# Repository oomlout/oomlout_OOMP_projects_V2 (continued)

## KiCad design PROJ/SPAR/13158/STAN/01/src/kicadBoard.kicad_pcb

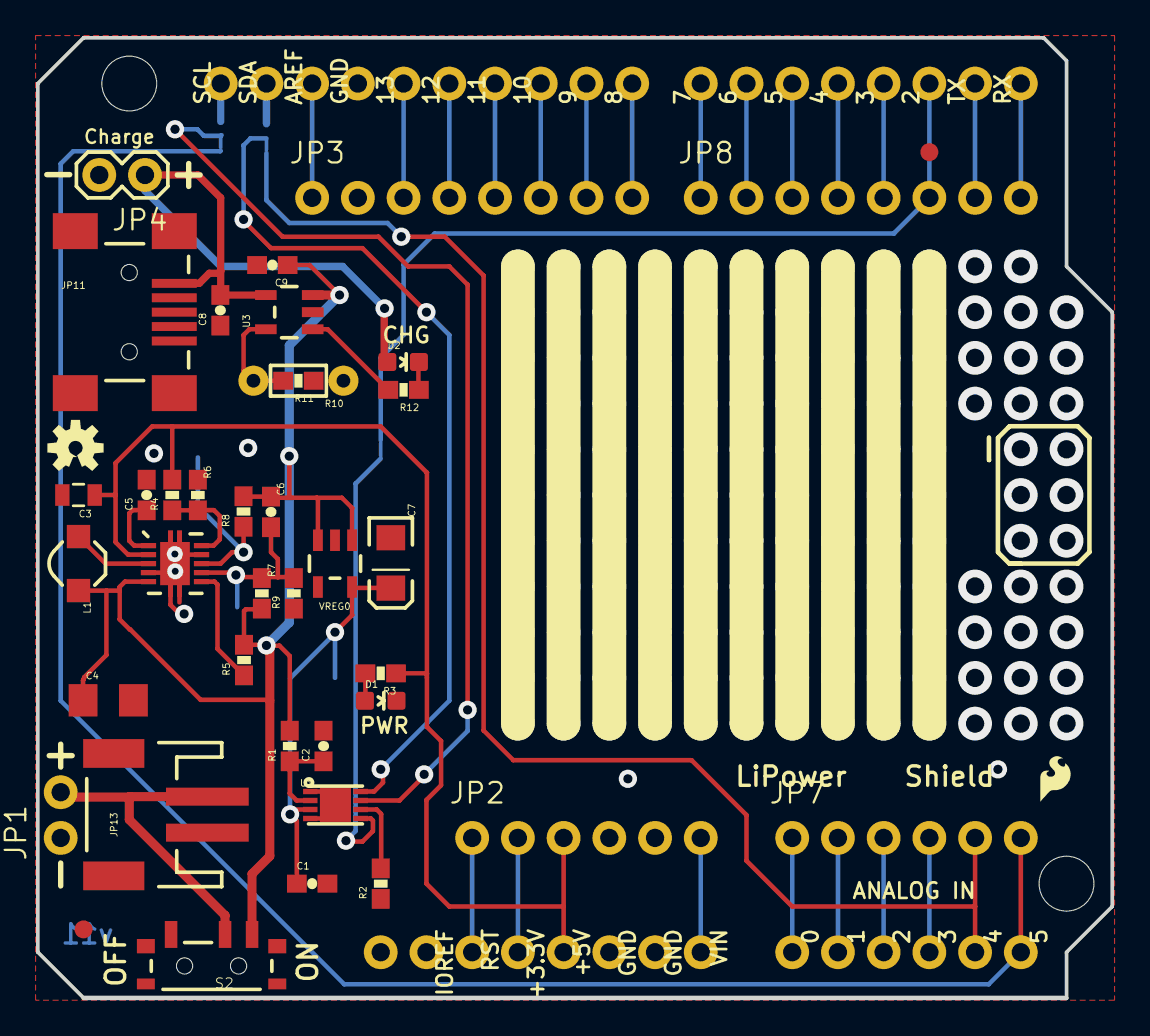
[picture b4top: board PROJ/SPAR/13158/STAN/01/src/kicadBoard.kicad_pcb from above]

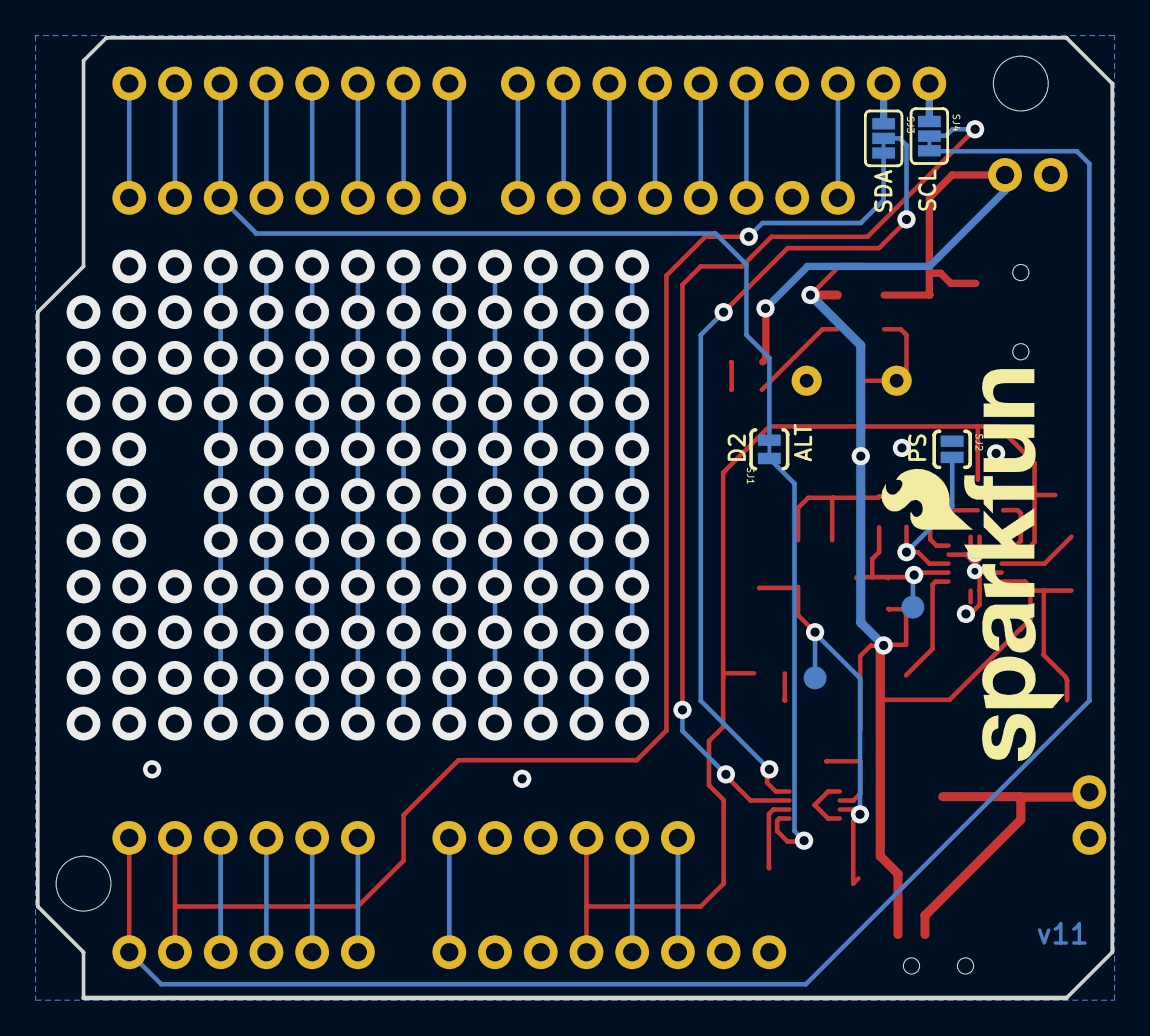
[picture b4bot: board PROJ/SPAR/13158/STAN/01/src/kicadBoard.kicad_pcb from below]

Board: 2 copper layers, 59.7 x 53.3 mm, 52 parts (7 on the bottom side), 47 nets.

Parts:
C1: 10nF; 0603-CAP
C2: 1uF; 0603-CAP
C3: 22uF; 0805
C4: 10uF; 1206
C5, C6: 0.1uF; 0603-CAP
C7: 10uF; EIA3216
C8, C9: 4.7uF; 0603-CAP
D1, D2: RED; LED-0603
FID1, FID2: FIDUCIAL1X2; FIDUCIAL-1X2
FRAME1: FRAME-LETTER; CREATIVE_COMMONS
JP1: 1X02_NO_SILK
JP2, JP7: 1X06_NO_SILK
JP3, JP8: 1X08_NO_SILK
JP4: M02PTH; 1X02
JP9, JP10: STAND-OFFTIGHT; STAND-OFF-TIGHT
JP11: USBSMD; USB-MINIB
JP13: JST-2-SMD
L1: 4.7uH, 1.2A; INDUCTOR_4.7UH
LOGO1: OSHW-LOGOS; OSHW-LOGO-S
LOGO2: SFE_LOGO_NAME_FLAME.2_INCH; SFE_LOGO_NAME_FLAME_.2
LOGO3: SFE_LOGO_FLAME.1_INCH; SFE_LOGO_FLAME_.1
R1: 1k; 0603-RES
R2: 4.7k; 0603-RES
R3, R12: 330; 0603-RES
R4: 2M; 0603-RES
R5, R8, R11: 10k; 0603-RES
R6: 220k; 0603-RES
R7: 2.0M; 0603-RES
R9: 200k; 0603-RES
R10: DNP; 1_6W-RES
S2: SWITCH-SPST-SMD-A
SJ1: SOLDERJUMPERTRACE; SJ_2S-TRACE
SJ2: PS; SJ_2S-NO
SJ3: SDA; PAD-JUMPER-3-2OF3_NC_BY_TRACE_YES_SILK_FULL_BOX
SJ4: SCL; PAD-JUMPER-3-2OF3_NC_BY_TRACE_YES_SILK_FULL_BOX
TP1, TP2: TEST-POINT3X5; PAD.03X.05
U1: MAX17043G+U; TDFN-8
U2: TPS61200; QFN-10_PAD
U3: MCP73831; SOT23-5
U4: ARDUINO_R3_SHIELD; UNO_R3_SHIELD
VREG0: MIC5205-3.3V; SOT23-5

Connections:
3.3-ARDUINO: JP2.2, U4.3.3V
3.3V: C1.1, C7.A, TP2.P$1, U1.3, VREG0.5
5V: C3.1, JP2.3, R3.1, R4.2, U2.2, U4.5V
A0: JP7.1, U4.A0
A1: JP7.2, U4.A1
A2: JP7.3, U4.A2
A3: JP7.4, U4.A3
ALT: SJ1.1, U1.5
AREF: JP3.1, U4.AREF
CELL: C2.1, R1.1, U1.2
D2: JP8.6, SJ1.2, U4.D2
D3: JP8.5, U4.D3
D4: JP8.4, U4.D4
D5: JP8.3, U4.D5
D6: JP8.2, U4.D6
D7: JP8.1, U4.D7
D8: JP3.8, U4.D8
D9: JP3.7, U4.D9
D10: JP3.6, U4.D10
D11: JP3.5, U4.D11
D12: JP3.4, U4.D12
D13: JP3.3, U4.D13
EN: R5.1, U2.6
FB: R4.1, R6.2, U2.10
GND: C1.2, C2.2, C3.2, C4.2, C5.2, C7.C, C8.1, C9.2, D1.C, JP1.1, JP2.4, JP2.5, JP3.2, JP4.2, JP11.GND, JP13.1, R2.1, R6.1, R9.1, R10.1, R11.1, SJ2.1, U1.1, U1.4, U1.EP, U2.4, U2.9, U2.11, U2.12, U2.13, U2.14, U2.15, U3.2, U4.GND@0, U4.GND@1, U4.GND@2, VREG0.2
unnamed: D1.A, R3.2
unnamed: L1.P$1, U2.3
unnamed: C5.1, U2.1
unnamed: D2.C, R12.1
unnamed: JP1.2, JP13.2, S2.2
unnamed: SJ3.2, U1.8
PROG: R10.2, R11.2, U3.5
PS: R8.1, SJ2.2, U2.8
QST: R2.2, U1.6
RST: JP2.1, U4.RES
RX: JP8.8, U4.RX
SCL: SJ4.2, U1.7
SCL-A5: JP7.6, SJ4.3, U4.A5
SCL-R3: SJ4.1, U4.SCL
SDA-A4: JP7.5, SJ3.3, U4.A4
SDA-R3: SJ3.1, U4.SDA
STAT: R12.2, U3.1
TX: JP8.7, U4.TX
UVLO: C6.2, R7.1, R9.2, TP1.P$1, U2.7
VBATT: C4.1, C6.1, C9.1, L1.P$2, R1.2, R5.2, R7.2, R8.2, S2.1, U2.5, U3.3, VREG0.1, VREG0.3
VBUS: C8.2, D2.A, JP4.1, JP11.VBUS, U3.4
VIN: JP2.6, U4.VIN

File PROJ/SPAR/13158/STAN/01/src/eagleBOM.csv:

"Part";"Value";"Device";"Package";"Description";"PROD-ID";"PROD_ID";"VALUE";
"C1";"10nF";"10NF/10000PF-50V-10%(0603)";"0603-CAP";"CAP-00867";"";"CAP-00867";"10nF";
"C2";"1uF";"1.0UF-16V-10%(0603)";"0603-CAP";"CAP-00868";"";"CAP-00868";"1.0uF";
"C3";"22uF";"22UF-6.3V-20%(0805)";"0805";"CAP-08402";"";"CAP-08402";"22uF";
"C4";"10uF";"10UF-6.3V-20%(1206)";"1206";"CAP-10057";"";"CAP-10057";"10uF";
"C5";"0.1uF";"0.1UF-25V(+80/-20%)(0603)";"0603-CAP";"CAP-00810";"";"CAP-00810";"0.1uF";
"C6";"0.1uF";"0.1UF-25V(+80/-20%)(0603)";"0603-CAP";"CAP-00810";"";"CAP-00810";"0.1uF";
"C7";"10uF";"10UF-16V-10%(TANT)";"EIA3216";"CAP-00811";"";"CAP-00811";"10uF";
"C8";"4.7uF";"4.7UF-6.3V-10%(0603)0603";"0603-CAP";"CAP-08280";"";"CAP-08280";"4.7uF";
"C9";"4.7uF";"4.7UF-6.3V-10%(0603)0603";"0603-CAP";"CAP-08280";"";"CAP-08280";"4.7uF";
"D1";"RED";"LED-RED0603";"LED-0603";"Assorted Red LEDs";"";"DIO-00819";"RED";
"D2";"RED";"LED-RED0603";"LED-0603";"Assorted Red LEDs";"";"DIO-00819";"RED";
"FID1";"FIDUCIAL1X2";"FIDUCIAL1X2";"FIDUCIAL-1X2";"Fiducial Alignment Points";"";"";"";
"FID2";"FIDUCIAL1X2";"FIDUCIAL1X2";"FIDUCIAL-1X2";"Fiducial Alignment Points";"";"";"";
"FRAME1";"FRAME-LETTER";"FRAME-LETTER";"CREATIVE_COMMONS";"Schematic Frame";"";"";"";
"JP1";"";"M021X02_NO_SILK";"1X02_NO_SILK";"Header 2";"";"";"";
"JP2";"";"M06NO_SILK";"1X06_NO_SILK";"Header 6";"";"";"";
"JP3";"";"M08NO_SILK";"1X08_NO_SILK";"Header 8";"";"";"";
"JP4";"M02PTH";"M02PTH";"1X02";"Standard 2-pin 0.1" header. Use with";"";"";"";
"JP7";"";"M06NO_SILK";"1X06_NO_SILK";"Header 6";"";"";"";
"JP8";"";"M08NO_SILK";"1X08_NO_SILK";"Header 8";"";"";"";
"JP9";"STAND-OFFTIGHT";"STAND-OFFTIGHT";"STAND-OFF-TIGHT";"Stand Off";"";"";"";
"JP10";"STAND-OFFTIGHT";"STAND-OFFTIGHT";"STAND-OFF-TIGHT";"Stand Off";"";"";"";
"JP11";"USBSMD";"USBSMD";"USB-MINIB";"USB Connectors";"";"CONN-08193";"";
"JP13";"";"JST_2MM_MALE";"JST-2-SMD";"Mates to single-cell LiPo batteries.";"";"CONN-08352";"";
"L1";"4.7uH, 1.2A";"INDUCTORINDUCTOR_4.7UH";"INDUCTOR_4.7UH";"Inductors";"";"NDUC-10146";"";
"LOGO1";"OSHW-LOGOS";"OSHW-LOGOS";"OSHW-LOGO-S";"Open Source Hardware Logo This logo indicates the piece of hardware it is found on incorporates a OSHW license and/or adheres to the definition of open source hardware found here: http://freedomdefined.org/OSHW";"";"";"";
"LOGO2";"SFE_LOGO_NAME_FLAME.2_INCH";"SFE_LOGO_NAME_FLAME.2_INCH";"SFE_LOGO_NAME_FLAME_.2";"SFE Logo, name and flame";"";"";"";
"LOGO3";"SFE_LOGO_FLAME.1_INCH";"SFE_LOGO_FLAME.1_INCH";"SFE_LOGO_FLAME_.1";"SFE Logo, flame only";"";"";"";
"R1";"1k";"1KOHM1/10W1%(0603)";"0603-RES";"RES-07856";"";"RES-07856";"1K";
"R2";"4.7k";"4.7KOHM1/10W1%(0603)";"0603-RES";"RES-07857";"";"RES-07857";"4.7K";
"R3";"330";"330OHM1/10W1%(0603)";"0603-RES";"RES-00818";"";"RES-00818";"330";
"R4";"2M";"2MOHMS-1/10W-1%(0603)";"0603-RES";"RES-10054";"";"RES-10054";"2.0M";
"R5";"10k";"10KOHM1/10W1%(0603)0603";"0603-RES";"RES-00824";"";"RES-00824";"10K";
"R6";"220k";"220KOHM1/10W1%(0603)";"0603-RES";"RES-08969";"";"RES-08969";"220k";
"R7";"2.0M";"2MOHMS-1/10W-1%(0603)";"0603-RES";"RES-10054";"";"RES-10054";"2.0M";
"R8";"10k";"10KOHM1/10W1%(0603)0603";"0603-RES";"RES-00824";"";"RES-00824";"10K";
"R9";"200k";"200KOHM1/10W1%(0603)200K";"0603-RES";"RES-09385";"";"RES-09385";"200k";
"R10";"DNP";"RESISTORPTH-1/6W";"1/6W-RES";"Resistor";"";"";"";
"R11";"10k";"10KOHM1/10W1%(0603)0603";"0603-RES";"RES-00824";"";"RES-00824";"10K";
"R12";"330";"330OHM1/10W1%(0603)";"0603-RES";"RES-00818";"";"RES-00818";"330";
"S2";"";"SWITCH-SPDT-SMD-A";"SWITCH-SPST-SMD-A";"SPDT Switch";"";"";"";
"SJ1";"SOLDERJUMPERTRACE";"SOLDERJUMPERTRACE";"SJ_2S-TRACE";"Solder Jumper";"";"";"";
"SJ2";"PS";"SOLDERJUMPERNO";"SJ_2S-NO";"Solder Jumper";"";"";"";
"SJ3";"SDA";"JUMPER-PAD-3-2OF3_NC_BY_TRACE";"PAD-JUMPER-3-2OF3_NC_BY_TRACE_YES_SILK_FULL_BOX";"";"";"";"";
"SJ4";"SCL";"JUMPER-PAD-3-2OF3_NC_BY_TRACE";"PAD-JUMPER-3-2OF3_NC_BY_TRACE_YES_SILK_FULL_BOX";"";"";"";"";
"TP1";"TEST-POINT3X5";"TEST-POINT3X5";"PAD.03X.05";"Bare copper test points for troubleshooting or ICT";"";"";"";
"TP2";"TEST-POINT3X5";"TEST-POINT3X5";"PAD.03X.05";"Bare copper test points for troubleshooting or ICT";"";"";"";
"U1";"MAX17043G+U";"MAX1704X";"TDFN-8";"MAX17043/MAX17044: Battery Fuel Guage (43 is 1cell, 44 is 2cell)";"IC-10399";"";"";
"U2";"TPS61200";"TPS61200";"QFN-10_PAD";"DC to DC Booster";"";"IC-10035";"";
"U3";"MCP73831";"MCP73831";"SOT23-5";"Miniature single cell, fully integrated Li-Ion, Li-polymer charge management controller";"";"IC-09995";"";
"U4";"ARDUINO_R3_SHIELD";"ARDUINO_R3_SHIELD";"UNO_R3_SHIELD";"Shield form compatible with the Arduino Uno R3.";"";"";"";
"VREG";"MIC5205-3.3V";"MIC52053.3V";"SOT23-5";"MIC5205 150mA vreg";"";"VREG-00822";"";

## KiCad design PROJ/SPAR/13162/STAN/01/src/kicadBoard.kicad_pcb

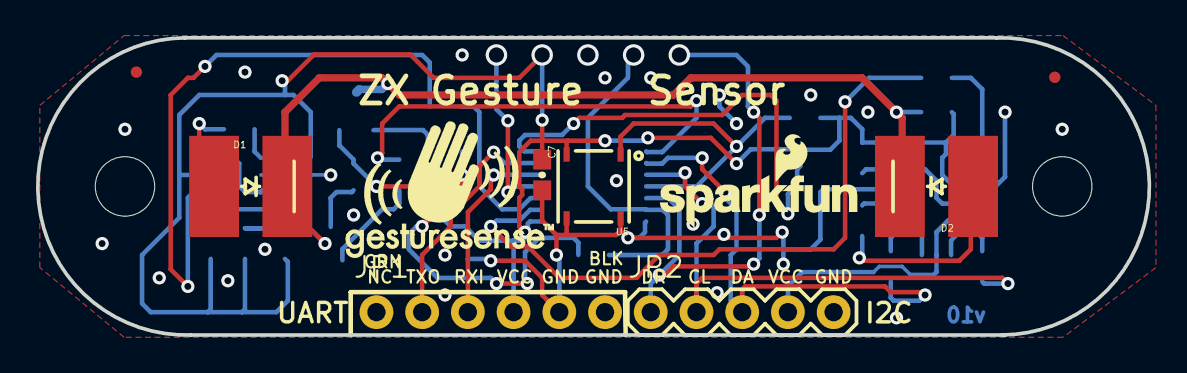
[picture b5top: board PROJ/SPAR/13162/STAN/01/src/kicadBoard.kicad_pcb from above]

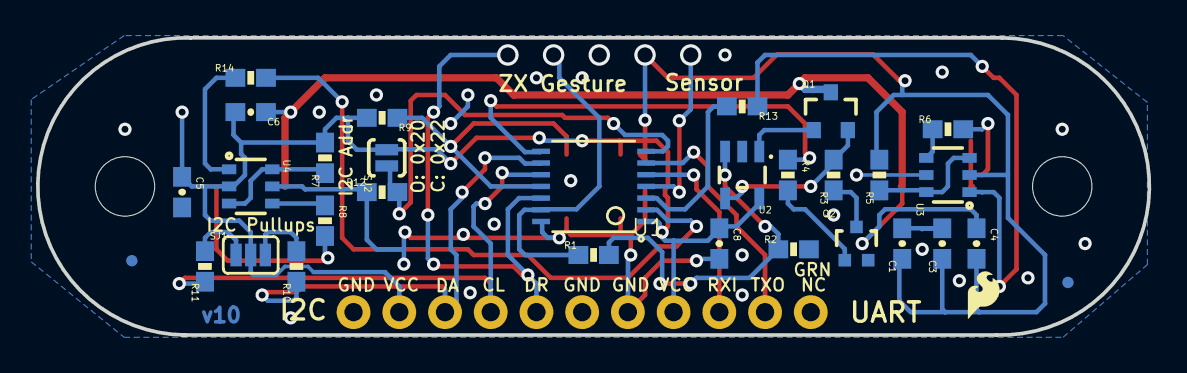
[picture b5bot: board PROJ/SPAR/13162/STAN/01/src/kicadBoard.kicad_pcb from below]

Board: 4 copper layers, 61.8 x 16.5 mm, 50 parts (36 on the bottom side), 30 nets.

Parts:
C1, C3, C5, C8: 0.1uF; 0603-CAP
C4, C6: 10nF; 0603-CAP
C7: 4.7uF; 0603-CAP
D1, D2: SFH4641SHORT2; SFH4641-SHORT2
FID1, FID2, FID3, FID4: FIDUCIALUFIDUCIAL; MICRO-FIDUCIAL
FRAME1: FRAME-LETTER; CREATIVE_COMMONS
JP1: 1X06_NO_SILK
JP2: 1X05
LOGO1: REVISION
LOGO2: SFE_LOGO_FLAME.1_INCH; SFE_LOGO_FLAME_.1
Q1: MMBT2222A; SOT23-3
Q2: MOSFET-NCHANNEL2N7002PW; SOT323
R1, R2, R5, R7: 100k; 0603-RES
R3: 1K 1%; 0603-RES
R4, R9, R13, R14: 1K; 0603-RES
R6, R8: 1; 0603-RES
R10, R11: 4.7K; 0603-RES
R12: 10K; 0603-RES
SJ1: JUMPER-PAD-3-NC_BY_PASTE; PAD-JUMPER-3-NC_BY_PASTE_YES_SILK_FULL_BOX
SJ2: JUMPER-PAD-2-NOYES_SILK; PAD-JUMPER-2-NO_YES_SILK
STANDOFF1, STANDOFF2: STAND-OFF
TP1, TP2, TP3, TP4, TP5: TEST-POINT3X4; PAD.03X.04
U1: PIC16F1823-14PINTSSOP; TSSOP14
U2: MCP6021T-E/OT; SOT23-5
U3, U4: DMC2700UDM; SOT26
U5: TSSP57038; TSOP572
U$5: SFE_LOGO_NAME_FLAME.1_INCH; SFE_LOGO_NAME_FLAME_.1
U$6: GESTURESENSE_LOGOSTEXT; GESTURESENSE_TEXT

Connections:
CARRIER: R4.1, U1.8
COMMON: C4.1, C6.1, D1.C, D2.C, Q1.3
EM1: R13.2, U1.3
EM2: R14.2, U1.2
GND: C1.2, C3.2, C5.2, C7.2, C8.2, JP1.5, JP1.6, JP2.5, Q2.2, R2.2, R12.1, TP3.P$1, U1.14, U2.2, U3.S1, U4.S1, U5.6, U5.8
I2C_ADDR: R12.2, SJ2.1, U1.7
I2C_SCL: JP2.2, R11.1, U1.10
I2C_SDA: JP2.3, R10.1, U1.9
ICSPCLK/DATA_RDY: JP2.1, TP5.P$1, U1.12
ICSPDAT/DACOUT: R1.1, TP4.P$1, U1.13
MCLR: TP1.P$1, U1.4
unnamed: R1.2, R2.1, U2.3
unnamed: Q1.2, R3.2, U2.4
unnamed: Q1.1, U2.1
unnamed: Q2.3, R3.1
unnamed: Q2.1, R4.2
unnamed: R6.1, U3.D2
unnamed: D1.A, R6.2
unnamed: R5.1, U3.D1, U3.G2
unnamed: R7.1, U4.D1, U4.G2
unnamed: R10.2, SJ1.3
unnamed: R8.1, U4.D2
unnamed: D2.A, R8.2
unnamed: R11.2, SJ1.1
unnamed: R13.1, U3.G1
unnamed: R14.1, U4.G1
RECEIVER: R9.1, U1.11, U5.1
UART_RX: JP1.2, U1.6
UART_TX: JP1.3, U1.5
VCC: C1.1, C3.1, C4.2, C5.1, C6.2, C7.1, C8.1, JP1.4, JP2.4, R5.2, R7.2, R9.2, SJ1.2, SJ2.2, TP2.P$1, U1.1, U2.5, U3.S2, U4.S2, U5.5

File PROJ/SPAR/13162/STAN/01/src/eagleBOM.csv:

"Part";"Value";"Device";"Package";"Description";"PROD_ID";"VALUE";
"C1";"0.1uF";"0.1UF-25V(+80/-20%)(0603)";"0603-CAP";"CAP-00810";"CAP-00810";"0.1uF";
"C3";"0.1uF";"0.1UF-25V(+80/-20%)(0603)";"0603-CAP";"CAP-00810";"CAP-00810";"0.1uF";
"C4";"10nF";"10NF/10000PF-50V-10%(0603)";"0603-CAP";"CAP-00867";"CAP-00867";"10nF";
"C5";"0.1uF";"0.1UF-25V(+80/-20%)(0603)";"0603-CAP";"CAP-00810";"CAP-00810";"0.1uF";
"C6";"10nF";"10NF/10000PF-50V-10%(0603)";"0603-CAP";"CAP-00867";"CAP-00867";"10nF";
"C7";"4.7uF";"4.7UF-6.3V-10%(0603)0603";"0603-CAP";"CAP-08280";"CAP-08280";"4.7uF";
"C8";"0.1uF";"0.1UF-25V(+80/-20%)(0603)";"0603-CAP";"CAP-00810";"CAP-00810";"0.1uF";
"D1";"SFH4641SHORT2";"SFH4641SHORT2";"SFH4641-SHORT2";"";"DIO-11994";"";
"D2";"SFH4641SHORT2";"SFH4641SHORT2";"SFH4641-SHORT2";"";"DIO-11994";"";
"FID1";"FIDUCIALUFIDUCIAL";"FIDUCIALUFIDUCIAL";"MICRO-FIDUCIAL";"Fiducial Alignment Points";"";"";
"FID2";"FIDUCIALUFIDUCIAL";"FIDUCIALUFIDUCIAL";"MICRO-FIDUCIAL";"Fiducial Alignment Points";"";"";
"FID3";"FIDUCIALUFIDUCIAL";"FIDUCIALUFIDUCIAL";"MICRO-FIDUCIAL";"Fiducial Alignment Points";"";"";
"FID4";"FIDUCIALUFIDUCIAL";"FIDUCIALUFIDUCIAL";"MICRO-FIDUCIAL";"Fiducial Alignment Points";"";"";
"FRAME1";"FRAME-LETTER";"FRAME-LETTER";"CREATIVE_COMMONS";"Schematic Frame";"";"";
"JP1";"";"M06NO_SILK_FEMALE_PTH";"1X06_NO_SILK";"Header 6";"CONN-08437";"";
"JP2";"";"M05PTH";"1X05";"Header 5";"";"";
"LOGO1";"REVISION";"REVISION";"REVISION";"";"";"";
"LOGO2";"SFE_LOGO_FLAME.1_INCH";"SFE_LOGO_FLAME.1_INCH";"SFE_LOGO_FLAME_.1";"SFE Logo, flame only";"";"";
"Q1";"MMBT2222A";"TRANSISTOR_NPNMMBT2222A";"SOT23-3";"Generic NPN BJT";"TRANS-08049";"MMBT2222A";
"Q2";"MOSFET-NCHANNEL2N7002PW";"MOSFET-NCHANNEL2N7002PW";"SOT323";"Common NMOSFET Parts";"TRANS-11151";"";
"R1";"100k";"100KOHM-1/10W-1%(0603)";"0603-RES";"RES-07828";"RES-07828";"100k";
"R2";"100k";"100KOHM-1/10W-1%(0603)";"0603-RES";"RES-07828";"RES-07828";"100k";
"R3";"1K 1%";"1KOHM-1/10W-1%(0603)";"0603-RES";"RES-07856";"RES-07856";"1K";
"R4";"1K";"1KOHM-1/10W-1%(0603)";"0603-RES";"RES-07856";"RES-07856";"1K";
"R5";"100k";"100KOHM-1/10W-1%(0603)";"0603-RES";"RES-07828";"RES-07828";"100k";
"R6";"1";"1OHM1/10W1%(0603)";"0603-RES";"RES-08269";"RES-08269";"1";
"R7";"100k";"100KOHM-1/10W-1%(0603)";"0603-RES";"RES-07828";"RES-07828";"100k";
"R8";"1";"1OHM1/10W1%(0603)";"0603-RES";"RES-08269";"RES-08269";"1";
"R9";"1K";"1KOHM-1/10W-1%(0603)";"0603-RES";"RES-07856";"RES-07856";"1K";
"R10";"4.7K";"4.7KOHM-1/10W-1%(0603)";"0603-RES";"RES-07857";"RES-07857";"4.7K";
"R11";"4.7K";"4.7KOHM-1/10W-1%(0603)";"0603-RES";"RES-07857";"RES-07857";"4.7K";
"R12";"10K";"10KOHM-1/10W-1%(0603)0603";"0603-RES";"RES-00824";"RES-00824";"10K";
"R13";"1K";"1KOHM-1/10W-1%(0603)";"0603-RES";"RES-07856";"RES-07856";"1K";
"R14";"1K";"1KOHM-1/10W-1%(0603)";"0603-RES";"RES-07856";"RES-07856";"1K";
"SJ1";"JUMPER-PAD-3-NC_BY_PASTE";"JUMPER-PAD-3-NC_BY_PASTE";"PAD-JUMPER-3-NC_BY_PASTE_YES_SILK_FULL_BOX";"";"";"";
"SJ2";"JUMPER-PAD-2-NOYES_SILK";"JUMPER-PAD-2-NOYES_SILK";"PAD-JUMPER-2-NO_YES_SILK";"";"";"";
"STANDOFF1";"STAND-OFF";"STAND-OFF";"STAND-OFF";"#4 Stand Off";"";"";
"STANDOFF2";"STAND-OFF";"STAND-OFF";"STAND-OFF";"#4 Stand Off";"";"";
"TP1";"TEST-POINT3X4";"TEST-POINT3X4";"PAD.03X.04";"Bare copper test points for troubleshooting or ICT";"";"";
"TP2";"TEST-POINT3X4";"TEST-POINT3X4";"PAD.03X.04";"Bare copper test points for troubleshooting or ICT";"";"";
"TP3";"TEST-POINT3X4";"TEST-POINT3X4";"PAD.03X.04";"Bare copper test points for troubleshooting or ICT";"";"";
"TP4";"TEST-POINT3X4";"TEST-POINT3X4";"PAD.03X.04";"Bare copper test points for troubleshooting or ICT";"";"";
"TP5";"TEST-POINT3X4";"TEST-POINT3X4";"PAD.03X.04";"Bare copper test points for troubleshooting or ICT";"";"";
"U$5";"SFE_LOGO_NAME_FLAME.1_INCH";"SFE_LOGO_NAME_FLAME.1_INCH";"SFE_LOGO_NAME_FLAME_.1";"SFE Logo, name and flame";"";"";
"U$6";"GESTURESENSE_LOGOSTEXT";"GESTURESENSE_LOGOSTEXT";"GESTURESENSE_TEXT";"";"";"";
"U1";"PIC16F1823-14PINTSSOP";"PIC16F1823-14PINTSSOP";"TSSOP14";"";"IC-11992";"";
"U2";"MCP6021T-E/OT";"MCP6021T-E/OT";"SOT23-5";"Rail-to-rail input/output op-amp with 10 MHz bandwidth.";"IC-12504";"";
"U3";"DMC2700UDM";"DMC2700UDM";"SOT26";"";"TRANS-11993";"";
"U4";"DMC2700UDM";"DMC2700UDM";"SOT26";"";"TRANS-11993";"";
"U5";"TSSP57038";"TSSP57038";"TSOP572";"";"PROD-13609";"";

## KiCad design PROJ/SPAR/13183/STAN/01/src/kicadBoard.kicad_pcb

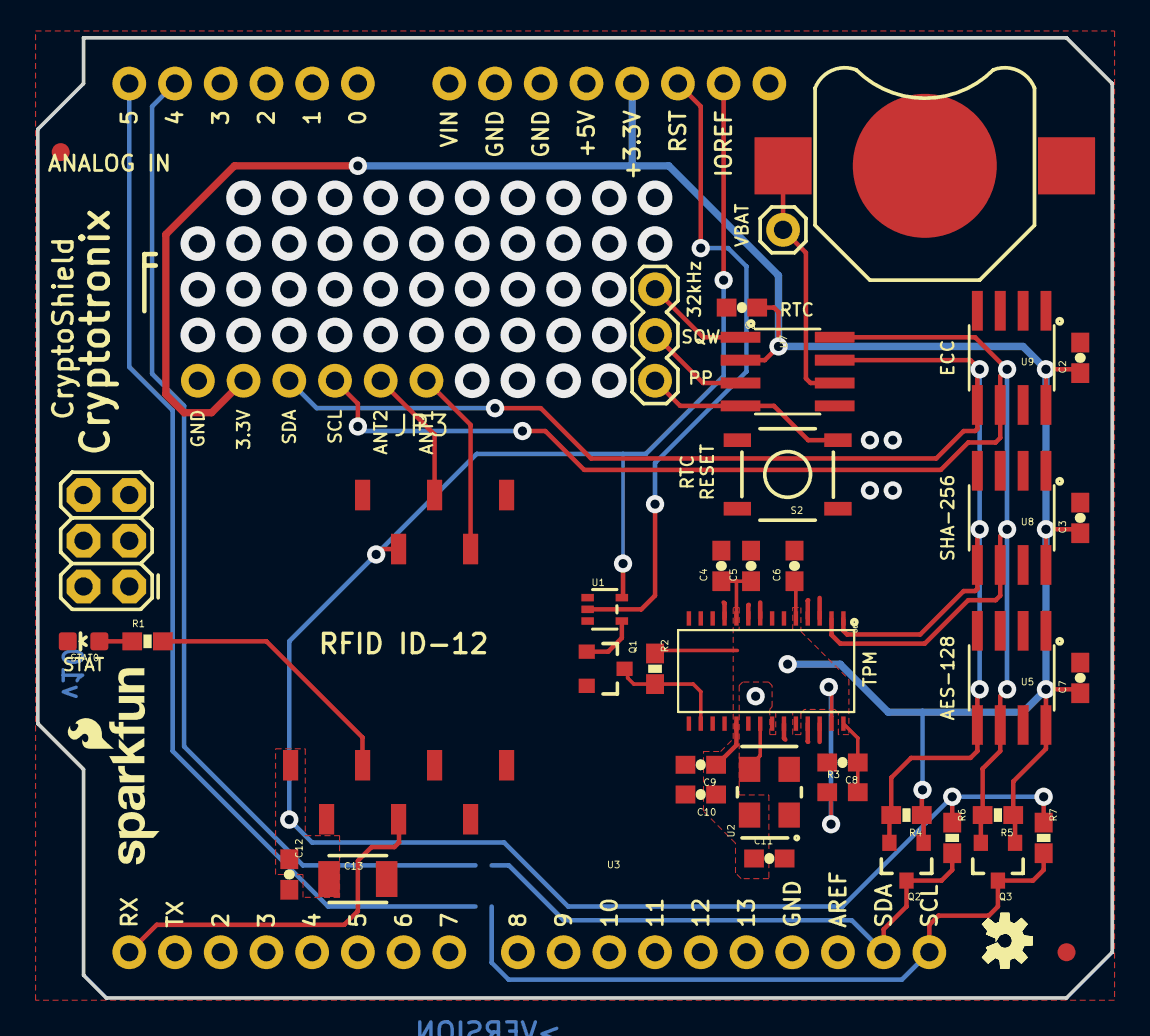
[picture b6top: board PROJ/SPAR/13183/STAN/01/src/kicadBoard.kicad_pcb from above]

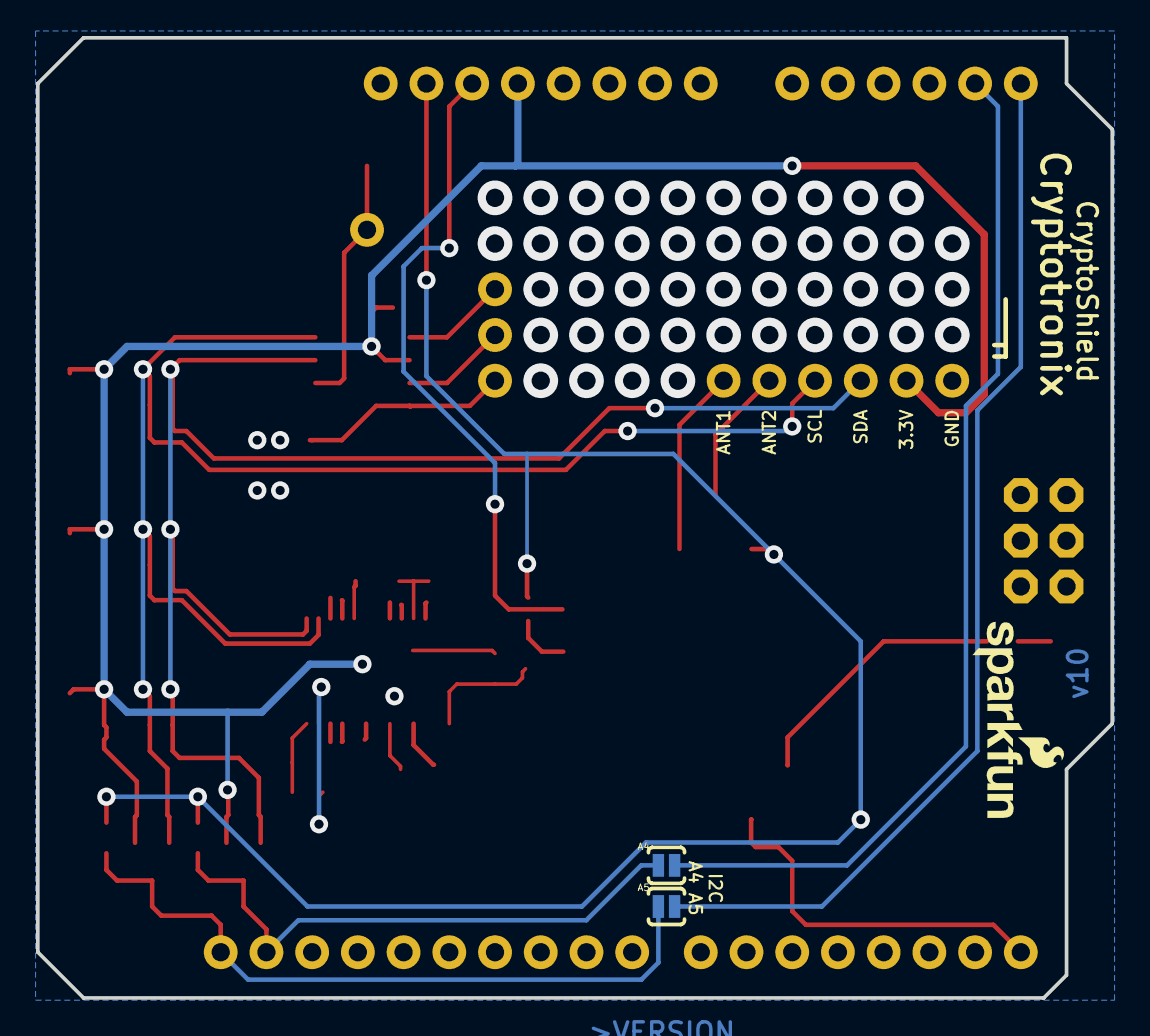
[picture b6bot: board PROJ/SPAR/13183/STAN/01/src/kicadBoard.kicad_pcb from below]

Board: 2 copper layers, 59.7 x 53.3 mm, 48 parts (3 on the bottom side), 23 nets.

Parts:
A4, A5: PAD-JUMPER-2-NO_YES_SILK
BAT1: 3V; BATTCON_12MM
C1, C2, C3, C7, C12: 0.1uF; 0603-CAP
C4, C10, C11: .1uf; 0603-CAP
C5, C6, C8, C9: 2200pf; 0603-CAP
C13: 10uF; 1210
FID1, FID2: FIDUCIAL1X2; FIDUCIAL-1X2
FRAME2: CREATIVE_COMMONS
J1: AVR_SPI_PRG_6PTH; 2X3
JP1: M01PTH; 1X01
JP2: 1X03
JP3: 1X06_NO_SILK
LOGO2: OSHW-LOGOS; OSHW-LOGO-S
LOGO3: SFE_LOGO_NAME_FLAME.1_INCH; SFE_LOGO_NAME_FLAME_.1
Q1, Q2, Q3: BSS138; SOT23-3
R1: 1k; 0603-RES
R2, R4, R5, R6, R7: 10K; 0603-RES
R3: 4.7K; 0603
S2: Reset; TACTILE-SWITCH-SMD
STAT0: GREEN; LED-0603
U1: 74LVC1G04; SOT353
U2: 33mhz; CRYSTAL-OSC-SMD-5X3.2
U3: ID-12/20SMD; ID-12_SMD
U4: ARDUINO_R3_SHIELD; UNO_R3_SHIELD
U5: ATAES132; SOIC8
U6: AT97SC3204T; TSSOP28
U7: DS3231M; SOIC8
U8: ATSHA204_SOIC8; SOIC8
U9: ATECC108; SOIC8
U$3: OSHW-LOGO-S
U$101: SFE_LOGO_NAME_FLAME_.1

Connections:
3.3V: C1.1, C2.1, C3.1, C4.1, C5.1, C6.1, C7.1, C8.1, C9.1, C10.1, C11.1, JP3.5, Q2.1, Q3.1, R2.1, R3.2, R4.1, R5.1, U2.4, U4.3.3V, U5.8, U6.5, U6.10, U6.19, U6.22, U6.24, U6.28, U7.2, U8.8, U9.8
32KHZ: JP2.1, U7.1
ANT1: JP3.2, U3.3
ANT2: JP3.1, U3.4
GND: BAT1.GND, C1.2, C2.2, C3.2, C4.2, C5.2, C6.2, C7.2, C8.2, C9.2, C10.2, C11.2, C12.2, C13.2, JP3.6, Q1.2, S2.1, STAT0.C, U1.3, U2.2, U3.1, U3.7, U4.GND@0, U4.GND@1, U4.GND@2, U5.4, U6.3, U6.4, U6.8, U6.9, U6.11, U6.15, U6.17, U6.18, U6.20, U6.23, U6.25, U6.26, U7.5, U8.4, U9.4
unnamed: R1.2, U3.10
unnamed: A4.2, U4.A4
unnamed: A5.2, U4.A5
unnamed: R1.1, STAT0.A
unnamed: Q1.3, R2.2, U6.16
unnamed: R3.1, U6.27
unnamed: Q1.1, U1.4
PP: JP2.3, S2.3, U7.4
RX: U3.9, U4.RX
SCL: JP3.3, Q3.2, R5.2, U5.6, U6.2, U7.8, U8.6, U9.6
SCL_IN: A5.1, Q3.3, R7.2, U4.SCL
SDA: JP3.4, Q2.2, R4.2, U5.5, U6.1, U7.7, U8.5, U9.5
SDA_IN: A4.1, Q2.3, R6.2, U4.SDA
SQW: JP2.2, U7.3
TPM_CLK: U2.3, U6.21
VBAT: BAT1.PWR@1, JP1.1, U7.6
VCCIO: C12.1, C13.1, R6.1, R7.1, U1.5, U3.2, U3.11, U4.IOREF
~RESET: U1.2, U4.RES

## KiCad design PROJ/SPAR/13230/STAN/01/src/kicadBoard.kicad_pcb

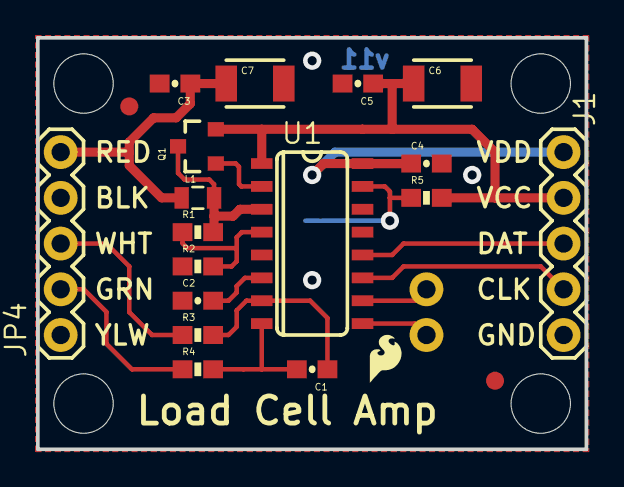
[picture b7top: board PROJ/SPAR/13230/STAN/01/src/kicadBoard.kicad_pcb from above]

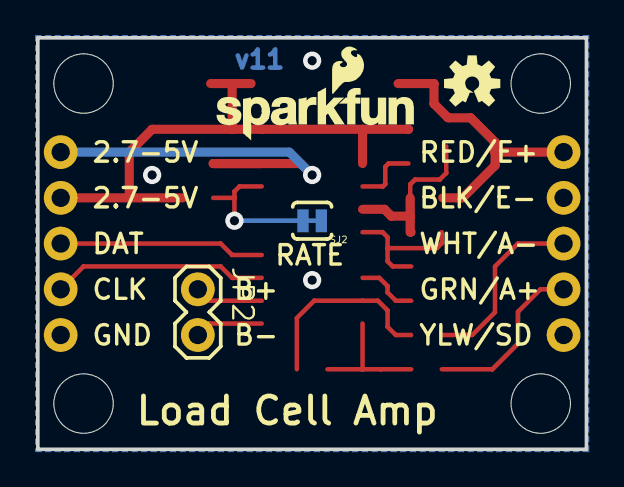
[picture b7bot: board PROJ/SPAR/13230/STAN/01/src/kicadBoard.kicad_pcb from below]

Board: 2 copper layers, 30.5 x 22.9 mm, 30 parts (4 on the bottom side), 17 nets.

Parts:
C1, C2, C3, C4, C5: 0.1uF; 0603-CAP
C6, C7: 10uF; 1210
FID1, FID2: FIDUCIAL1X2; FIDUCIAL-1X2
FRAME1: FRAME-LETTER; CREATIVE_COMMONS
J1: 1X05
JP2: 1X02
JP4: 1X05
L1: 3.3uH; 0805
LOGO1: SFE_LOGO_NAME_FLAME.1_INCH; SFE_LOGO_NAME_FLAME_.1
LOGO3: SFE_LOGO_FLAME.1_INCH; SFE_LOGO_FLAME_.1
Q1: MMBT4403; SOT23-3
R1: 20k; 0603-RES
R2: 8.2K; 0603-RES
R3, R4: 100; 0603-RES
R5: 10K; 0603-RES
SJ2: PAD-JUMPER-2-NC_BY_TRACE_YES_SILK
STANDOFF1, STANDOFF2, STANDOFF3, STANDOFF4: STAND-OFF
U1: HX711; SO16
U7: OSHW-LOGOS; OSHW-LOGO-S
U$1: REVISION

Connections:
A+: JP4.2, R4.1
A-: JP4.3, R3.1
AVDD: C3.1, C7.1, JP4.5, L1.1
B+: JP2.1, U1.10
B-: JP2.2, U1.9
DAT: J1.3, U1.12
GND: C2.1, C3.2, C4.2, C5.2, C6.2, C7.2, J1.5, JP4.1, JP4.4, R2.1, SJ2.1, U1.5, U1.14
unnamed: R5.1, SJ2.2, U1.15
unnamed: C1.1, R3.2, U1.7
unnamed: C1.2, R4.2, U1.8
unnamed: Q1.1, U1.2
unnamed: L1.2, Q1.3, R1.2, U1.3
unnamed: R1.1, R2.2, U1.4
unnamed: C2.2, U1.6
SCK: J1.4, U1.11
VCC: C5.1, C6.1, J1.2, Q1.2, R5.2, U1.1
VDD: C4.1, J1.1, U1.16
